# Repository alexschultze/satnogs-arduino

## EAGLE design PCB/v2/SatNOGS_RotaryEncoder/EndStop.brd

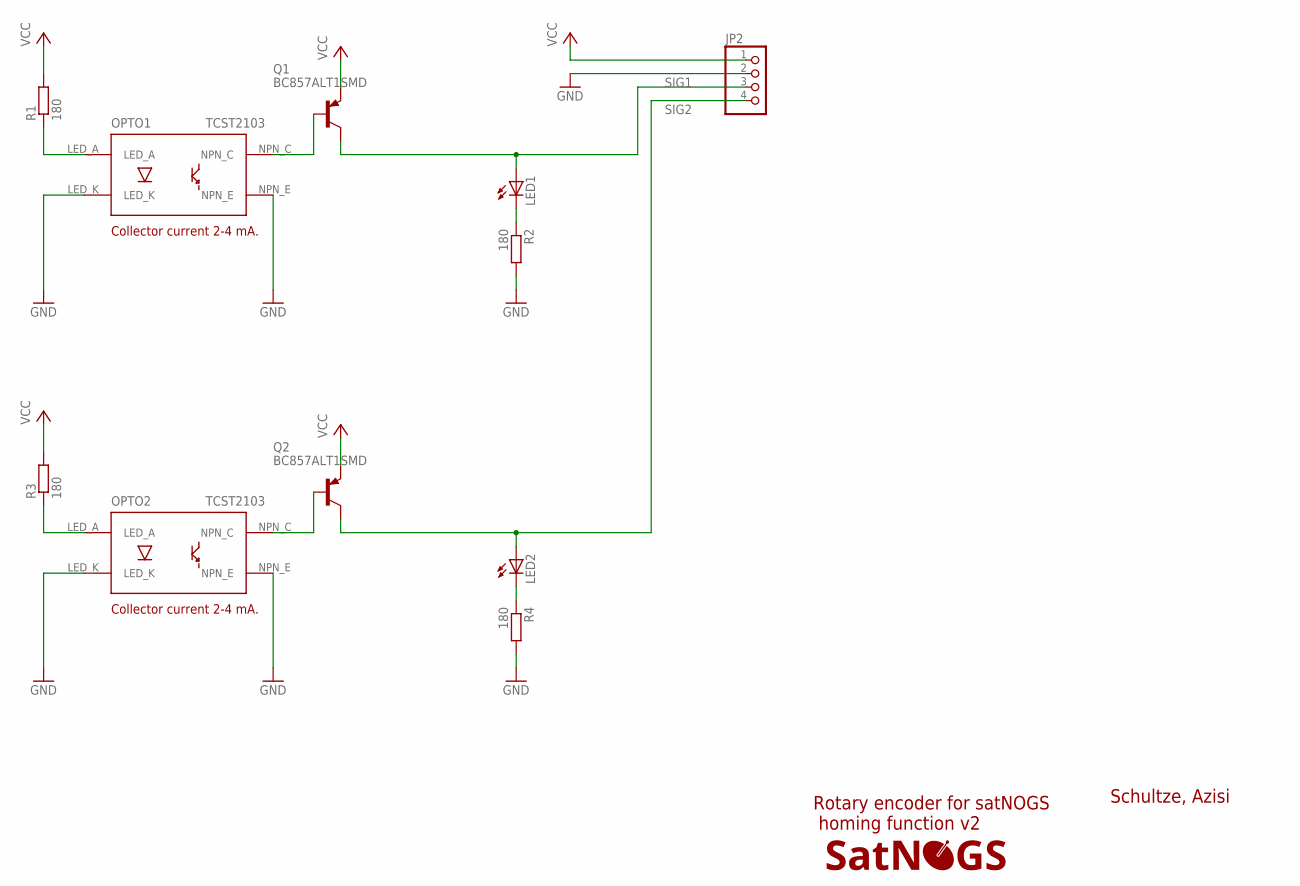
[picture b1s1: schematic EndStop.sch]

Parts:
JP2: PINHD-1X4; 1X04
LED1, LED2: LED3MM
LOGO1: SATNOGS_LOGOSILK_XS; LOGO_SILK_XS
OPTO1, OPTO2: TCST2103; TCST2013
Q1, Q2: BC857ALT1SMD; SOT23-BEC
R1, R2, R3, R4: 180; R0805

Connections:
GND: JP2.2, OPTO1.LED_K, OPTO1.NPN_E, OPTO2.LED_K, OPTO2.NPN_E, R2.2, R4.2
unnamed: OPTO2.LED_A, R3.1
unnamed: OPTO1.LED_A, R1.1
unnamed: LED1.K (C), R2.1
unnamed: OPTO1.NPN_C, Q1.B
unnamed: LED2.K (C), R4.1
unnamed: OPTO2.NPN_C, Q2.B
SIG1: JP2.3, LED1.A, Q1.C
SIG2: JP2.4, LED2.A, Q2.C
VCC: JP2.1, Q1.E, Q2.E, R1.2, R3.2

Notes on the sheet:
Schultze, Azisi
Rotary encoder for satNOGS homing function v2
Collector current 2-4 mA.

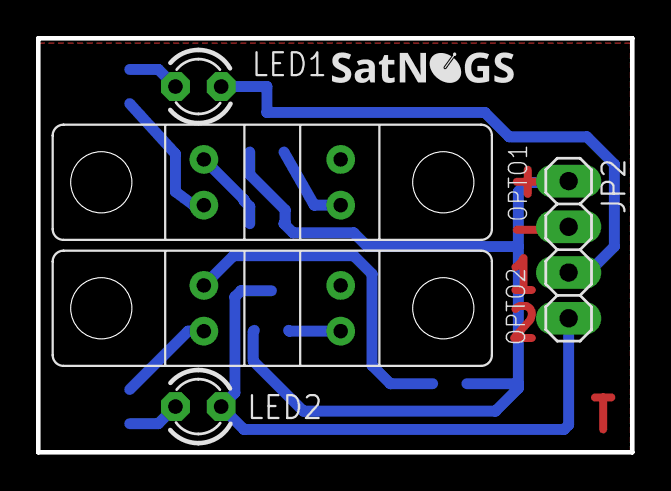
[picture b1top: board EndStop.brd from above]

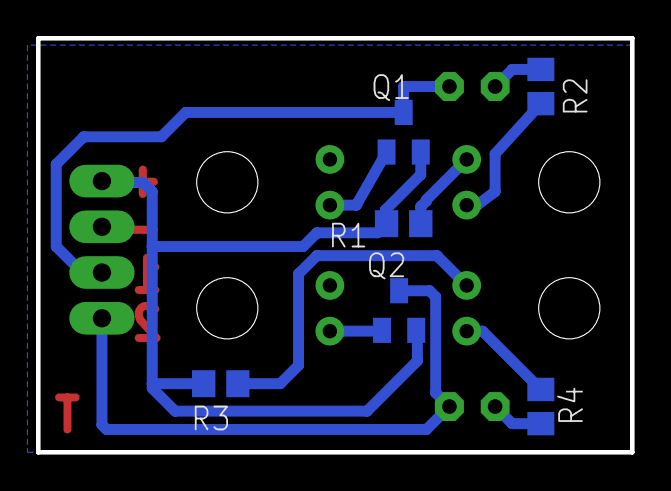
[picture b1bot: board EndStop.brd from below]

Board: 2 copper layers, 33.0 x 23.0 mm, 12 parts (6 on the bottom side), 10 nets.

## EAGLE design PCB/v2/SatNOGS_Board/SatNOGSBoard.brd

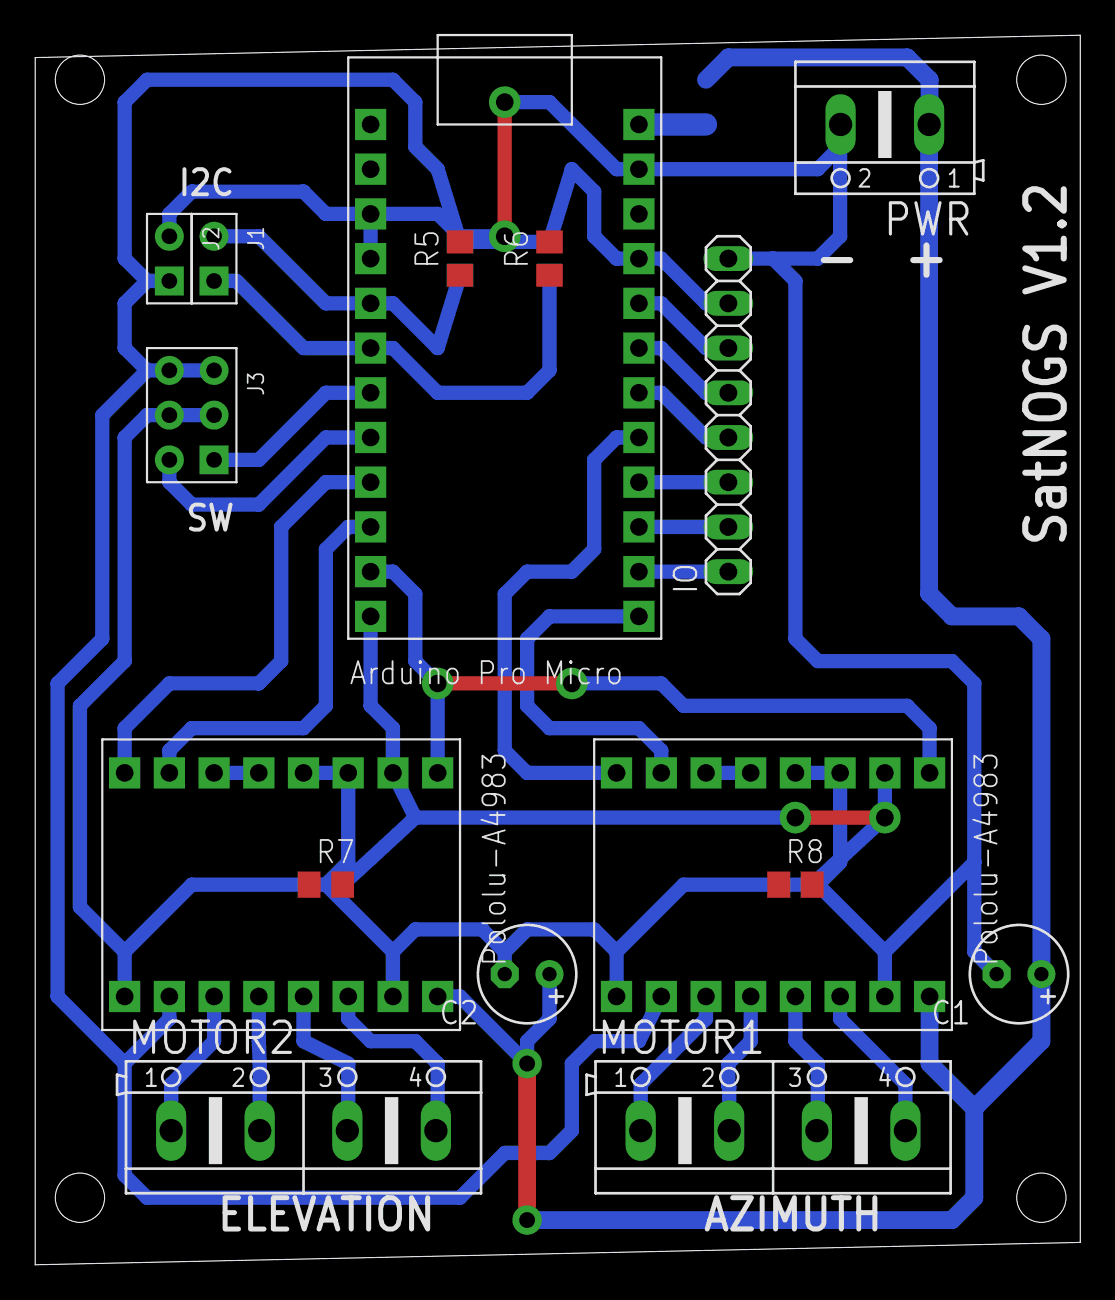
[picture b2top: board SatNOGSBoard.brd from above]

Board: 2 copper layers, 59.4 x 69.8 mm, 18 parts (1 on the bottom side), 30 nets.

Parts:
AZIMUTH: POLOLU-A4983POLOLU-A4983; POLOLU-A4983
C1, C2: 100uF; E2,5-6
ELEVATION: POLOLU-A4983POLOLU-A4983; POLOLU-A4983
IO: 1; 1X08
J1: 2; 2P-2.54-65/35MIL
J2: 3; 2P-2.54-65/35MIL
J3: 4; 2X3P-2.54-65/35MIL
MOTOR1: 2; AK500/4
MOTOR2: 3; AK500/4
PWR: 1; AK500/2
R5, R6: 10k; R0805
R7, R8: 100k; R0805
SJ1: SJ1; SJW
U$1: SATNOGS_LOGORESTRICT_M; LOGO_RESTRICT_M
UC: ARDUINO_PRO_MICROARDUINO_BOARD; ARDUINO_MICRO_PRO

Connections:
1-1A: AZIMUTH.12, MOTOR1.2
1-1B: AZIMUTH.11, MOTOR1.1
1-2A: AZIMUTH.13, MOTOR1.3
1-2B: AZIMUTH.14, MOTOR1.4
2-1A: ELEVATION.12, MOTOR2.2
2-1B: ELEVATION.11, MOTOR2.1
2-2A: ELEVATION.13, MOTOR2.3
2-2B: ELEVATION.14, MOTOR2.4
DIR-1: AZIMUTH.8, UC.17
DIR-2: ELEVATION.8, UC.9
GND: AZIMUTH.3, AZIMUTH.4, AZIMUTH.9, AZIMUTH.15, C1.-, C2.-, ELEVATION.3, ELEVATION.4, ELEVATION.9, ELEVATION.15, IO.8, J2.2, J3.2, J3.5, PWR.2, R7.1, R8.1, UC.3, UC.4, UC.23
IO1: IO.6, UC.20
IO2: IO.5, UC.19
IO3: IO.4, UC.18
IO4: IO.3, UC.16
IO5: IO.2, UC.15
IO6: IO.1, UC.14
MS1: AZIMUTH.2, ELEVATION.2, R7.2, R8.2, UC.12
M_EN: AZIMUTH.1, ELEVATION.1, UC.11
unnamed: AZIMUTH.5, AZIMUTH.6
unnamed: ELEVATION.5, ELEVATION.6
unnamed: SJ1.1, UC.24
SCL: J1.1, R6.1, UC.6
SDA: J1.2, R5.1, UC.5
STEP-1: AZIMUTH.7, UC.13
STEP-2: ELEVATION.7, UC.10
SW1: J3.1, UC.7
SW2: J3.6, UC.8
VCC: AZIMUTH.10, ELEVATION.10, IO.7, J2.1, J3.3, J3.4, R5.2, R6.2, UC.21
VMOTOR: AZIMUTH.16, C1.+, C2.+, ELEVATION.16, PWR.1, SJ1.2

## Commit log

2015-03-08 -add two new version of end stop (v2), add TSTC2103 signal amplifier -move extend library to include all board elements, update elements, include satnogs logo -include datasheets, design rule files -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
2015-03-16 implement rotatary gray code encoder with 2 optical sensors
